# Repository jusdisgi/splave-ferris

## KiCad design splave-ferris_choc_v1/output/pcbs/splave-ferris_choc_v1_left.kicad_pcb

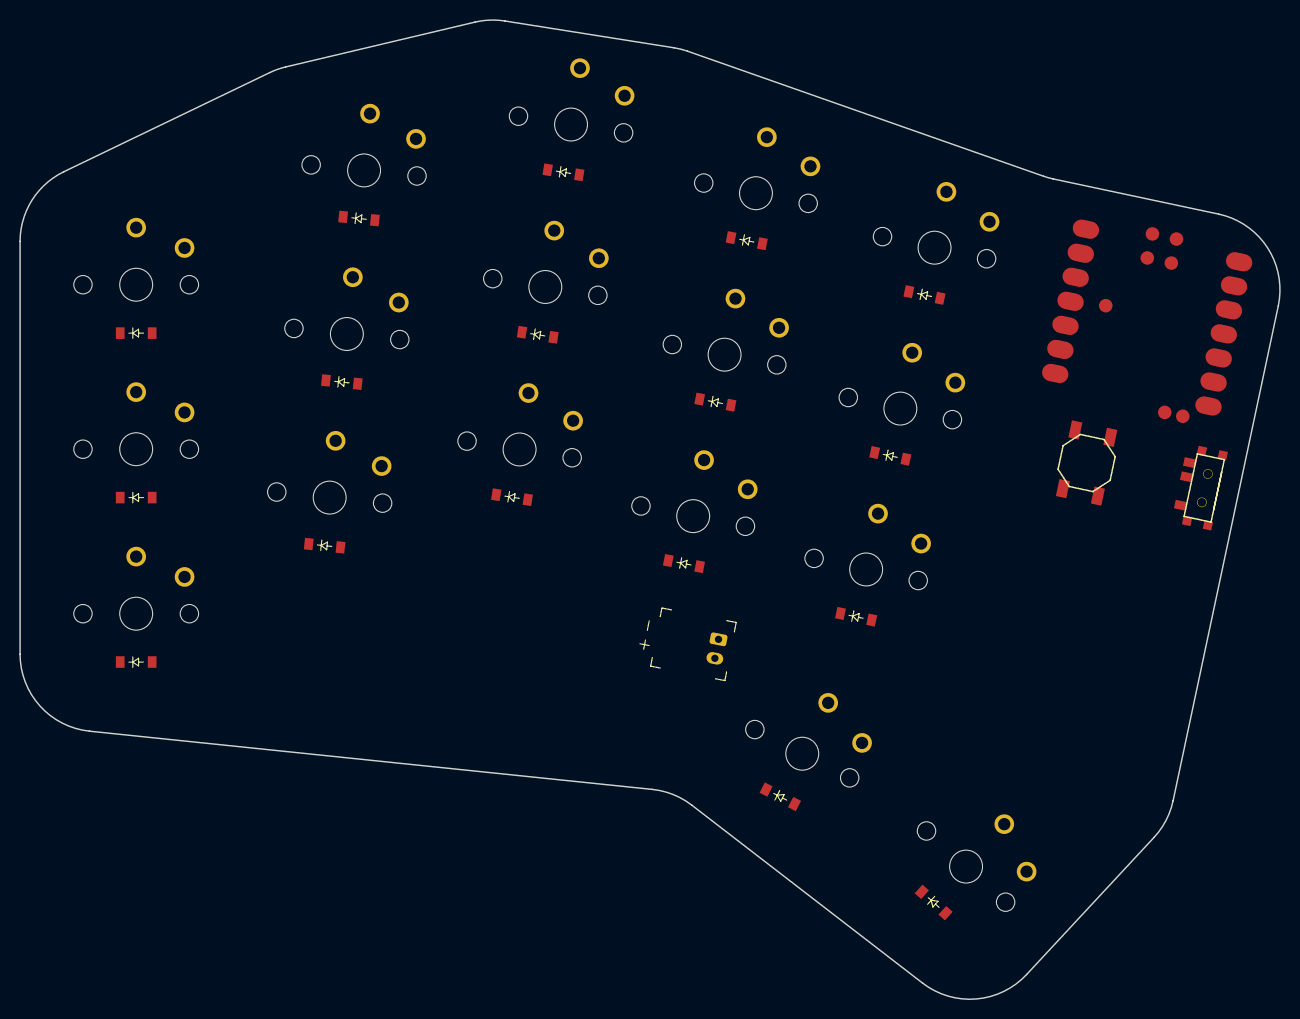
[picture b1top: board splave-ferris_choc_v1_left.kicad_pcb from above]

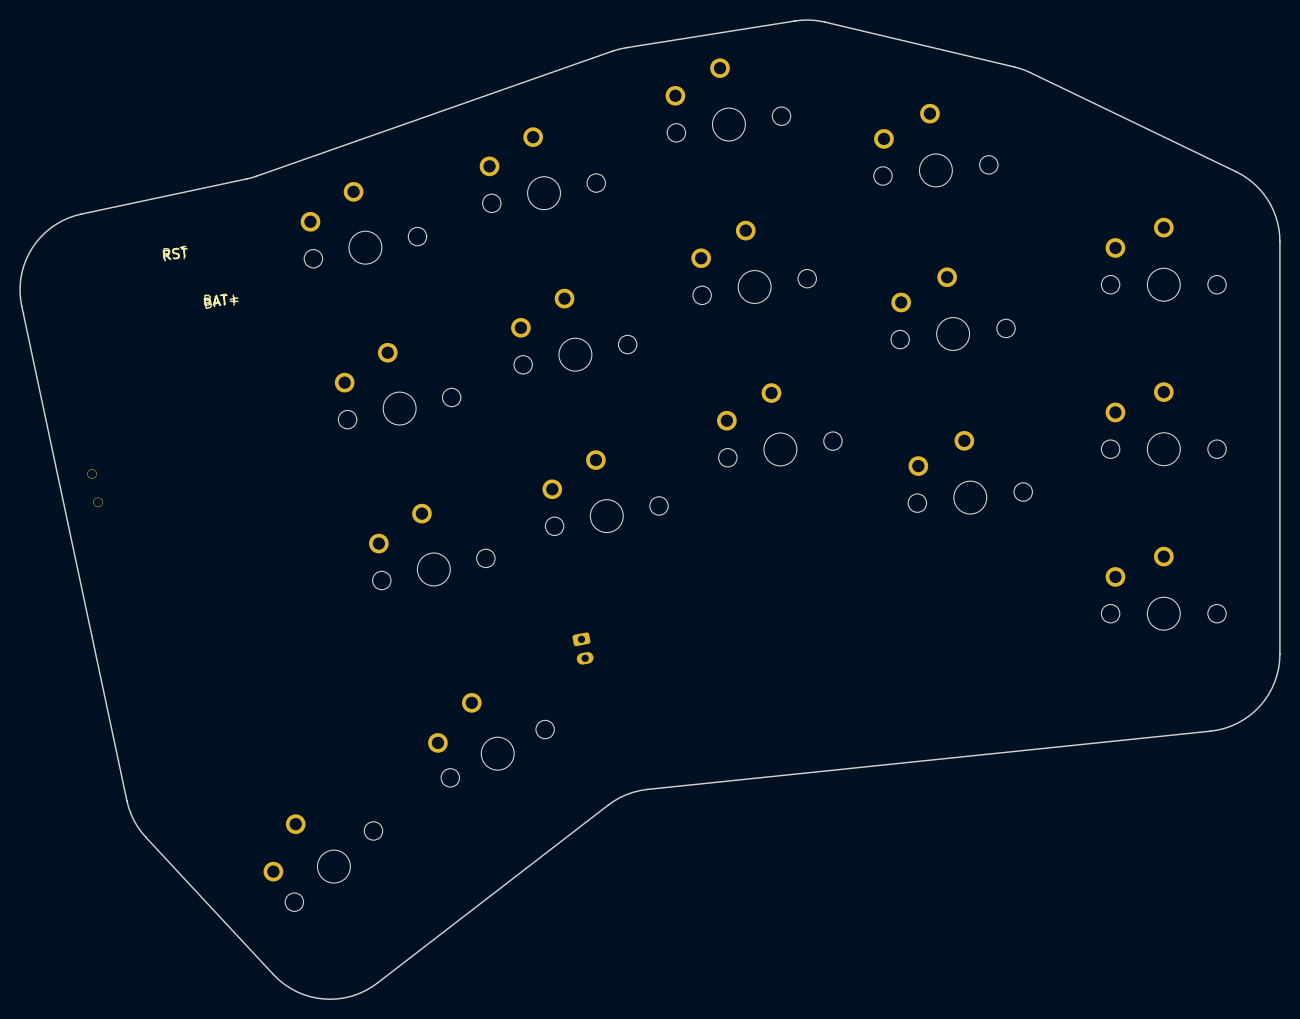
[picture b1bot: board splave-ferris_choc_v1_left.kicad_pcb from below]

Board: 2 copper layers, 130.2 x 101.2 mm, 38 parts (17 on the bottom side), 30 nets, no tracks yet.

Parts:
B1: SW_TACT_ALPS_SKQGABE010
D1, D2, D3, D4, D5, D6, D7, D8, D9, D10, D11, D12, D13, D14, D15, D16, D17: diode_tht_sod123
JST1: battery_connector_jst_ph_2
MCU1: xiao_smd
S1, S2, S3, S4, S5, S6, S7, S8, S9, S10, S11, S12, S13, S14, S15, S16, S17: switch_choc_v1_v2
T1: SPDT_C128955

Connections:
BAT: MCU1.19, T1.2
BATCON: JST1.2, T1.1
D0: D3.1, D6.1, D9.1, D12.1, D15.1, MCU1.1
D1: MCU1.2, S7.2, S8.2, S9.2
D2: MCU1.3, S4.2, S5.2, S6.2
D3: D2.1, D5.1, D8.1, D11.1, D14.1, MCU1.4
D4: MCU1.5, S1.2, S2.2, S3.2
D5: D1.1, D4.1, D7.1, D10.1, D13.1, MCU1.6
D8: MCU1.9, S13.2, S14.2, S15.2, S17.2
D9: D16.1, D17.1, MCU1.10
D10: MCU1.11, S10.2, S11.2, S12.2, S16.2
GND: B1.1, JST1.1, MCU1.13, MCU1.18
RST: B1.2, MCU1.17
far_fan: D17.2, S17.1
index_bottom: D10.2, S10.1
index_home: D11.2, S11.1
index_top: D12.2, S12.1
inner_bottom: D13.2, S13.1
inner_home: D14.2, S14.1
inner_top: D15.2, S15.1
middle_bottom: D7.2, S7.1
middle_home: D8.2, S8.1
middle_top: D9.2, S9.1
near_fan: D16.2, S16.1
pinky_bottom: D1.2, S1.1
pinky_home: D2.2, S2.1
pinky_top: D3.2, S3.1
ring_bottom: D4.2, S4.1
ring_home: D5.2, S5.1
ring_top: D6.2, S6.1

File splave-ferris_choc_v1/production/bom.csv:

Designator,Footprint,Quantity,Value,LCSC Part #
B1,SW_TACT_ALPS_SKQGABE010,1,,
"D1, D10, D11, D12, D13, D14, D15, D16, D17, D2, D3, D4, D5, D6, D7, D8, D9",diode_tht_sod123,17,,
JST1,battery_connector_jst_ph_2,1,,
MCU1,xiao_smd,1,,
T1,SPDT_C128955,1,,
